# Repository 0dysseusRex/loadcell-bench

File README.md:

# Load cell bench

The load cell bench is a browser app for checking a 4-wire load cell before it goes on a printer. It talks to a Plimsoll amplifier running Klipper over USB, or it runs a built-in simulator, and it measures three things: how fast the readings arrive, how straight they are against weights you already trust, and how much load the cell can take before the converter saturates or the zero fails to come back. You read those results, then you decide whether the cell is ready for a nozzle probe or an extrusion force trace.

AI disclaimer. This app, this readme, the wiki, and the Custom K2 Loadcell were written with the help of AI tools. Treat the pin maps, the cut file, the bending numbers, and the pass limits as a starting point. Measure the cell you built, and read the drawing, before you cut metal, order a board, or send the cell to a printer. A pass in the simulator is not a measurement of the metal.

The wiki walks every screen in the order you test a cell, with a screenshot of each one: [wiki/README.md](wiki/README.md). The Custom K2 Loadcell plate is a hardware sub-project there, with its own build guide.

A bench for any full-bridge load cell. The bridge plugs into a [Plimsoll](https://github.com/mulcmu/Plimsoll) ADC, which is either a mini board on a [FYSETC H36 Combo V2](https://github.com/FYSETC/H36_Combo_V2) or an alpha board with its own USB port. The K2 plate in this repo — laser-cut 6061-T6, four BA1000-3AA gauges, Loctite 401 under Loctite 9460 — is one worked example, not the only cell the tests accept.

The board runs Klipper. This program speaks Klipper’s USB protocol from the browser and counts the samples that come back. It is the check you run before the cell goes on a printer. Three fronts are wired up:

- H36 + mini ADS1220
- H36 + mini HX717
- Alpha USB + HX717 (STM32F072, SCLK PC1, DOUT PC2)

The 4-channel ADS131M04 under-bed board is not part of this bench.

## Run it

Chrome or Edge. Web Serial is how the page reaches the board. Firefox and Safari can still open the simulator.

```bash
npm install
npm run dev
```

Open [http://127.0.0.1:4471](http://127.0.0.1:4471).

A small launcher window can do that install, start the server, and open the page. On Windows, double-click `launcher/LoadCellBench.exe`.

- **Install** runs `npm install` and `npm run build`. The button then reads **Uninstall**, which removes `node_modules` and the Next.js build.
- **Run** starts the server on port 4471 and opens http://127.0.0.1:4471 in the default browser. Run again while it is up opens the page a second time.
- **Close** stops the server and closes the window. The title-bar button does the same.

Node.js 18.18 or newer has to be installed already. The launcher uses a Node that includes npm, and it skips a Node that was bundled with another tool when a normal install is on the machine.

On a Mac, double-click `launcher/Load Cell Bench.command`. That opens Terminal and the same window. On Linux, run `launcher/loadcell-bench.sh`. `launcher/build.sh` freezes a native binary on that computer. Linux also needs the `python3-tk` package for the window.

`npm test` checks the Klipper frame codec against Klipper’s own byte encoding, the ADS1220 register image, the HX717 gain channels, and the speed / accuracy / range math.

## What you can measure

- **Live.** Counts, grams after tare, noise, and a scrolling trace. On the ADS1220, auto gain walks 1× to 128× and stops before a bridge offset hits the rail. On the HX717 the gain is A-128 or A-64 and is chosen when you connect. Invert the sign if pressing the nozzle side goes the wrong way.
- **Speed.** Asks the ADS1220 for each sample rate, or times the HX717 against its solder-jumper choices (10, 20, 80, 320 Hz). A pass is within 8% of the setting, with no MCU overflows, no missing USB blocks, and counts that are not stuck. A real HX717 passes only the jumper that is fitted. The alpha board’s internal clock can also show up here as chip errors.
- **Accuracy.** Capture the empty cell and known masses, or type mass and counts from a notebook. The fit is counts = offset + counts-per-gram × mass. Unload the same masses for hysteresis, repeat one mass for scatter, and hold for 30 seconds to see adhesive creep.
- **Range.** Eight seconds unloaded for the noise floor, or a noise rms you type in counts. Then step the load until the ADC saturates or the zero does not come back. A rated capacity on the Build tab is the ceiling you set; it does not replace the return-to-zero check.

The Build tab has a bending calculator for the alloys load cells are usually cut from: 6061-T6, 2024-T3, 7075-T6, 17-4 PH H900, and alloy steel. You give it thickness and the neck width, length, and count. It reports Young's modulus, guided-leaf stiffness, and a yield load when the yield is known.

The bending calculator starts on the Custom K2 Loadcell: 6061-T6, 0.100 in, four necks, gauges on one face, and the simulator's starting scale. CUSTOM LOADCELL leaves the alloy, thickness, necks, and gauge blank. Save this cell downloads a file and keeps a copy in the browser. Upload that file on a later visit.

The Build tab also takes a DXF sketch. Click two points to fill a neck width or length, or click to place a gauge and see whether the grid fits the neck. DWG files need Save As DXF first. The click check is a fit, not a stress analysis.

The gauge card takes a preset — BA1000-3AA, BA1000-3A 1 kΩ, BA500-3AB in 350 Ω or 1 kΩ, BA300-3AF 350 Ω, BFL-350, BFL-1K, a 350 Ω foil, a generic 1 kΩ foil — or a custom factor. A half bridge or a quarter bridge scales the output for arms that are completion resistors. A scale you type, or a fit you apply, replaces the sketch in the simulator and on the live grams.

A guide along the left starts with the amp menu at the top right: pick the board, then Connect or Use simulator. After that it walks through naming the cell, the live counts, and speed, accuracy, and range. On a narrow screen that guide sits above the tabs and can be hidden. When those three tests have results, Compile results opens one page in plain language. Print it from the browser if you want a copy.

## Wire it

Flash the H36 for USB before connecting it here:

- Micro-controller: STM32
- Processor: STM32G431
- Bootloader offset: no bootloader
- Clock: 12 MHz crystal
- Communication: USB on PA11/PA12
- GPIO pins set at startup: `PA2`

Leave ADS1220 and software SPI enabled. Both are on in a normal Klipper build.

The Plimsoll mini ADS1220 on an H36 Combo V2 uses software SPI:

| Signal | Pin |
| --- | --- |
| CS | PA14 |
| DRDY | PA1 |
| SCLK | PB7 |
| MOSI | PA13 |
| MISO | PA15 |

PA13 is the MOSI pin on that header. PB13 is the heater MOSFET.

The mini HX717 on the same V2 header is not SPI. SCLK is PB7 and DOUT is PA15. The rate is a solder jumper, 320 Hz unless you moved it. Gain in the config is `A-128` or `A-64`.

The menu also has H36 Combo (v1). That 2×6 header is not the V2 header. The mini ADS1220 uses hardware SPI `spi1a`: CS PB6, DRDY PC13, SCLK PB3, MOSI PB5, MISO PB4. The mini HX717 uses SCLK PB3 and DOUT PB4. Flash the v1 board as STM32G0B1, USB on PA11/PA12, startup pin `PA2`.

The alpha board is its own MCU. Flash it as STM32F072, no bootloader, internal clock, USB on PA11/PA12. Optional startup pin PC7 for the power LED. The HX717 on that board uses SCLK PC1 and DOUT PC2. The internal clock is what the published sample config uses, and it can time out a probe; the speed test is where that shows up.

The four-conductor cable in the build photos (red, green, blue, black) lands on the mini board’s E+, E−, S+, and S− pads. This program does not assume which color is which. If the sign is backwards, invert it in the live panel. Do not swap excitation with signal.

Klipper on the printer and this bench cannot share the USB port. Disconnect here before starting the printer.

## After the bench

The Build tab downloads a `load_cell` snippet named after the cell, with the gain, rate, and, once you apply a calibration or type a scale, `counts_per_gram`. On the printer:

1. `LOAD_CELL_DIAGNOSTIC`
2. `LOAD_CELL_CALIBRATE`
3. `LOAD_CELL_TEST_TAP` before a real probe
4. Keep the nozzle near 140°C while probing so ooze is not the thing you touch

Pressure advance is not computed here. If the range test calls the cell a force-trace candidate (about 1.5 g of 3-sigma noise at 330 Hz or faster, and the zero comes back), an extrusion force trace is worth logging. Mainline Klipper does not turn that trace into a pressure-advance value by itself.

## The K2 plate

`hardware/NewLoadcell.dxf` is the cut file for the example cell. The plate is 38 × 24 mm, 0.100 in thick. The drawing is in millimeters. Other designs skip the DXF and type their own measurements. The plate and its build notes are a separate open-hardware project: [wiki/hardware/custom-k2-loadcell/README.md](wiki/hardware/custom-k2-loadcell/README.md).

## License

The bench application, the launcher, and the user guide are under the [MIT License](LICENSE).

The Custom K2 Loadcell design, the cut file, and the hardware pages in the wiki are under the [CERN Open Hardware Licence Version 2 - Permissive](hardware/LICENSE-CERN-OHL-P-2.0.txt). That is the permissive CERN hardware licence: you can study, modify, share, and make the plate, including in a product you sell. The full text is in that file, and CERN asks that it stay unmodified.

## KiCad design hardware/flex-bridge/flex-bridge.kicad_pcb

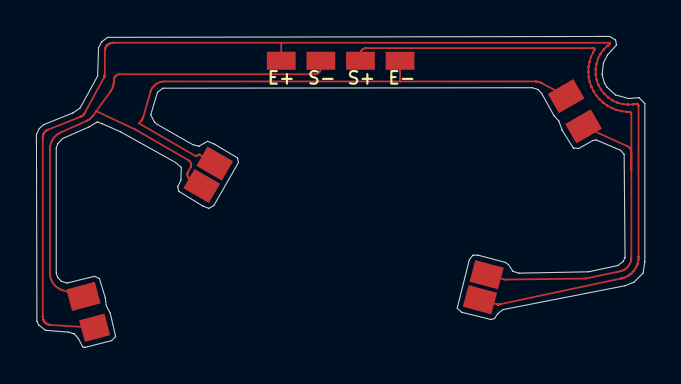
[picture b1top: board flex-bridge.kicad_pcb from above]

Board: 2 copper layers, 33.8 x 17.3 mm, 12 parts (0 on the bottom side), 4 nets.

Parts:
G1, G2, G3, G4, G5, G6, G7, G8: FlexPad
J1: E+; WirePad
J2: E-; WirePad
J3: S+; WirePad
J4: S-; WirePad

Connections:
E+: G1.1, G4.1, J1.1
E-: G6.1, G7.1, J2.1
S+: G3.1, G8.1, J3.1
S-: G2.1, G5.1, J4.1
